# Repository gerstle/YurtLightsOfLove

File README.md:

Yurt Lights of Love
=====

ambient lighting for the yurt.

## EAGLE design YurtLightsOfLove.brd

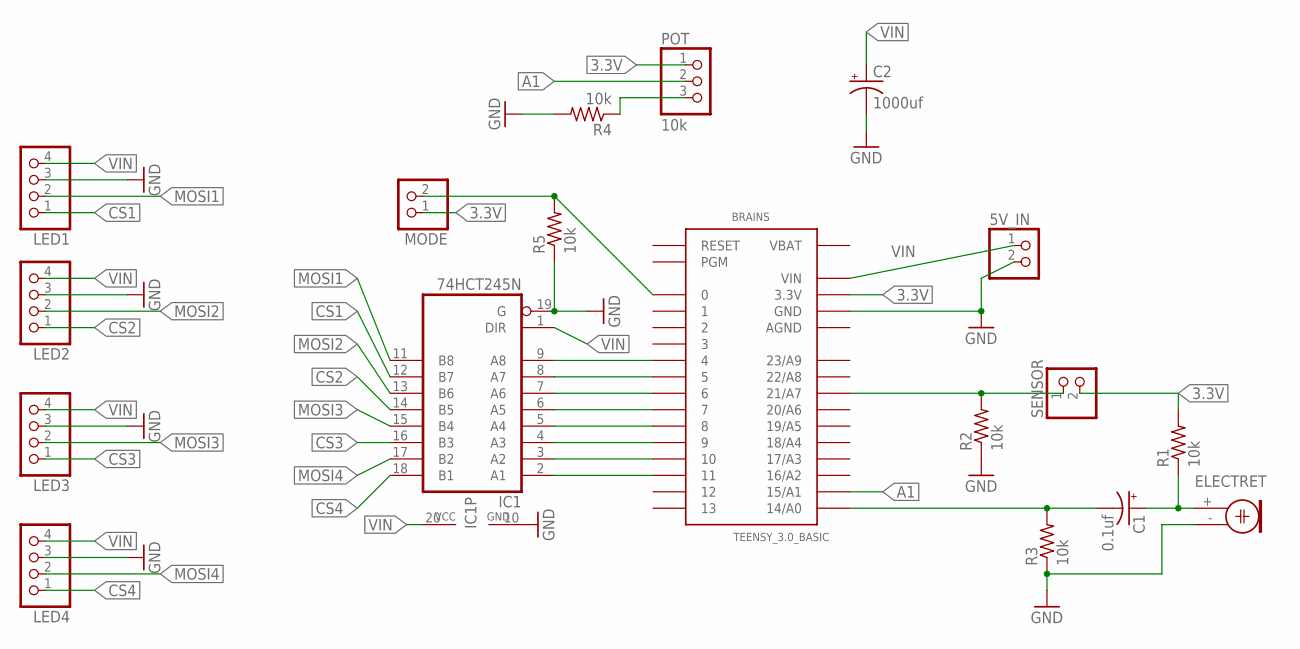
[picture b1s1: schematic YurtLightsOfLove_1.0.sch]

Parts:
5V_IN: PINHD-1X2; 1X02
BRAINS: TEENSY_3.0_BASIC
C1: 0.1uf; E5-5
C2: 1000uf; E3,5-8
ELECTRET: ELECTRET; 9.7ELECTRET
IC1: 74HCT245N; DIL20
LED1, LED2, LED3, LED4: PINHD-1X4; 1X04
MODE: PINHD-1X2; 1X02
POT: 10k; 1X03
R1, R2, R3, R4, R5: 10k; 0207/10
SENSOR: PINHD-1X2; 1X02

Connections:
3.3V: BRAINS.3.3V, BRAINS.3.3V1 (3.3V), MODE.1, POT.1, R1.2, SENSOR.2
A1: BRAINS.15/A1, POT.2
AGND: BRAINS.AGND
CS1: IC1.12 (B7), LED1.1
CS2: IC1.14 (B5), LED2.1
CS3: IC1.16 (B3), LED3.1
CS4: IC1.18 (B1), LED4.1
GND: 5V_IN.2, BRAINS.GND, BRAINS.GND1 (GND), C2.-, ELECTRET.- (1), IC1.10 (GND), IC1.19 (G), LED1.3, LED2.3, LED3.3, LED4.3, R2.1, R3.1, R4.2, R5.1
MOSI1: IC1.11 (B8), LED1.2
MOSI2: IC1.13 (B6), LED2.2
MOSI3: IC1.15 (B4), LED3.2
MOSI4: IC1.17 (B2), LED4.2
unnamed: BRAINS.4, IC1.9 (A8)
unnamed: BRAINS.5, IC1.8 (A7)
unnamed: BRAINS.6, IC1.7 (A6)
unnamed: BRAINS.7, IC1.6 (A5)
unnamed: BRAINS.8, IC1.5 (A4)
unnamed: BRAINS.9, IC1.4 (A3)
unnamed: BRAINS.10, IC1.3 (A2)
unnamed: BRAINS.11, IC1.2 (A1)
unnamed: C1.+, ELECTRET.+ (2), R1.1
unnamed: POT.3, R4.1
unnamed: BRAINS.14/A0, C1.-, R3.2
unnamed: BRAINS.0, MODE.2, R5.2
unnamed: BRAINS.21/A7, R2.2, SENSOR.1
VBAT: BRAINS.VBAT
VIN: 5V_IN.1, BRAINS.VIN, C2.+, IC1.1 (DIR), IC1.20 (VCC), LED1.4, LED2.4, LED3.4, LED4.4

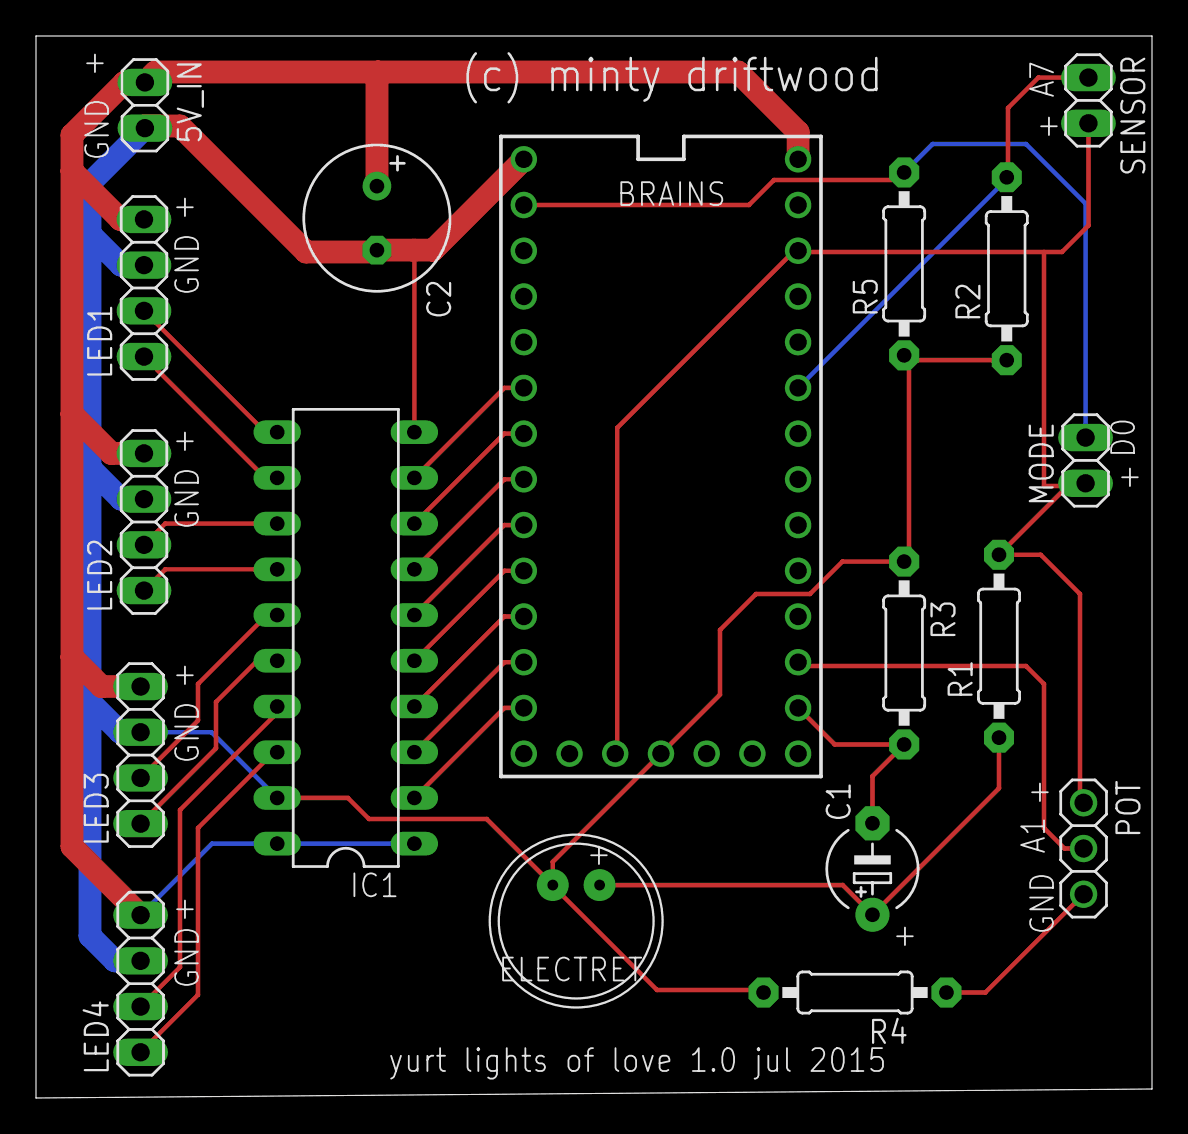
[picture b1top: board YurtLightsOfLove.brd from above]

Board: 2 copper layers, 62.0 x 59.0 mm, 18 parts (0 on the bottom side), 25 nets.

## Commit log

2015-08-05 1.0 board
2015-08-05 let's name things more appropriately
2015-08-10 initial
2015-08-14 brightness control and mode button working
2015-08-17 +close encounters, moon, & rainbow
2016-03-05 resolving remote
